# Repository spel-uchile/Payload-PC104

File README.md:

# Payload-PC104 #

This repository contains schematics and footprints of the PC104 standard for CubeSats' payloads. 
These designs are compatible with Eagle and KiCad PCB design software.
The footprints have also a suggested PCB boundary that facilitates the cable management of the CubeSat.

# KiCAD #

The KiCAD's schematic includes all the necessary pins assignments to speedup the payload design. The footprint already has the edge cuts done and it follows the PC104 specification.

# Last update 10/21/2021# 
Output voltage pin update on StackBreakout with Molex picoBlade

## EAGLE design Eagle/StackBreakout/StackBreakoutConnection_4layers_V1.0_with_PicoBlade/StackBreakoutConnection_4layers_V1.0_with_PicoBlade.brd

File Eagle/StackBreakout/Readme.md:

Readme - Stack Breakout

Stack Breakout - 4 capas

Historial

2021-11-24
Correción de error en conexión I2C v2. Los pines actuales son SCL (H1.9), SDA (H1.11). 
La versión anterior tiene las conexiones invertidas, es decir, el pin SCL estaba en H1.11, y SDA en H1.9.

2021-10-21
Se actualizan el orden los OUT pin de voltaje de acuerdo a la configuración de pinout de SPEL.

2020-08-12
Se incorpora conector con conexión I2C y UART.

2020-07-27 - V1.0
Se genera la placa de acuerdo a los diseños (dxf) enviados por Elías Obreque.
Se genera la placa usando cuatro capas
Se configurar parámetros genéricos (y más comunes) para el chequeo de errores (DRC - Design Rule Check)

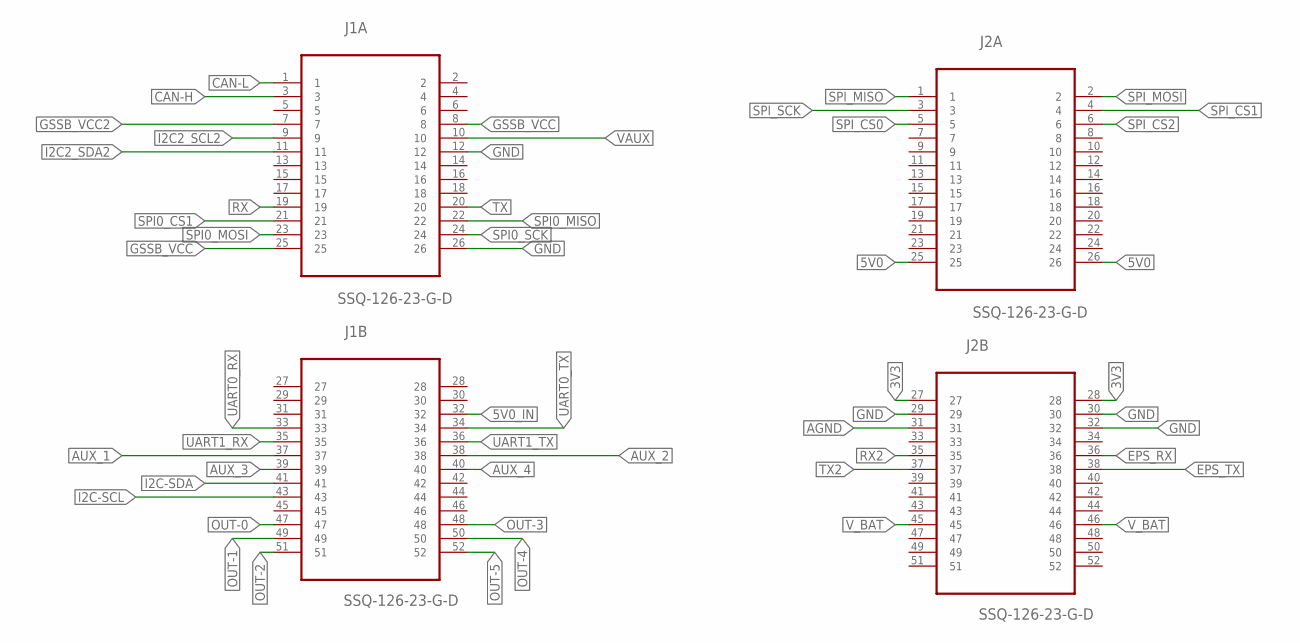
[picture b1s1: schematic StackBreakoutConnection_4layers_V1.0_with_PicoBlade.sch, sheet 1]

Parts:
J1, J2: SSQ-126-23-G-D; SAMTEC_SSQ-126-23-G-D

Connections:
3V3: J2.27, J2.28; also elsewhere on the board
5V0: J2.25, J2.26; also elsewhere on the board
5V0_IN: J1.32; also elsewhere on the board
AGND: J2.31; also elsewhere on the board
AUX_1: J1.37; also elsewhere on the board
AUX_2: J1.38; also elsewhere on the board
AUX_3: J1.39; also elsewhere on the board
AUX_4: J1.40; also elsewhere on the board
CAN-H: J1.3; also elsewhere on the board
CAN-L: J1.1; also elsewhere on the board
EPS_RX: J2.36; also elsewhere on the board
EPS_TX: J2.38; also elsewhere on the board
GND: J1.12, J1.26, J2.29, J2.30, J2.32; also elsewhere on the board
GSSB_VCC: J1.8, J1.25; also elsewhere on the board
GSSB_VCC2: J1.7; also elsewhere on the board
I2C2_SCL2: J1.9; also elsewhere on the board
I2C2_SDA2: J1.11; also elsewhere on the board
I2C-SCL: J1.43; also elsewhere on the board
I2C-SDA: J1.41; also elsewhere on the board
OUT-0: J1.47; also elsewhere on the board
OUT-1: J1.49; also elsewhere on the board
OUT-2: J1.51; also elsewhere on the board
OUT-3: J1.48; also elsewhere on the board
OUT-4: J1.50; also elsewhere on the board
OUT-5: J1.52; also elsewhere on the board
RX: J1.19
RX2: J2.35
SPI0_CS1: J1.21; also elsewhere on the board
SPI0_MISO: J1.22; also elsewhere on the board
SPI0_MOSI: J1.23; also elsewhere on the board
SPI0_SCK: J1.24; also elsewhere on the board
SPI_CS0: J2.5
SPI_CS1: J2.4
SPI_CS2: J2.6
SPI_MISO: J2.1
SPI_MOSI: J2.2
SPI_SCK: J2.3
TX: J1.20
TX2: J2.37
UART0_RX: J1.33; also elsewhere on the board
UART0_TX: J1.34; also elsewhere on the board
UART1_RX: J1.35; also elsewhere on the board
UART1_TX: J1.36; also elsewhere on the board
VAUX: J1.10; also elsewhere on the board
V_BAT: J2.45, J2.46; also elsewhere on the board

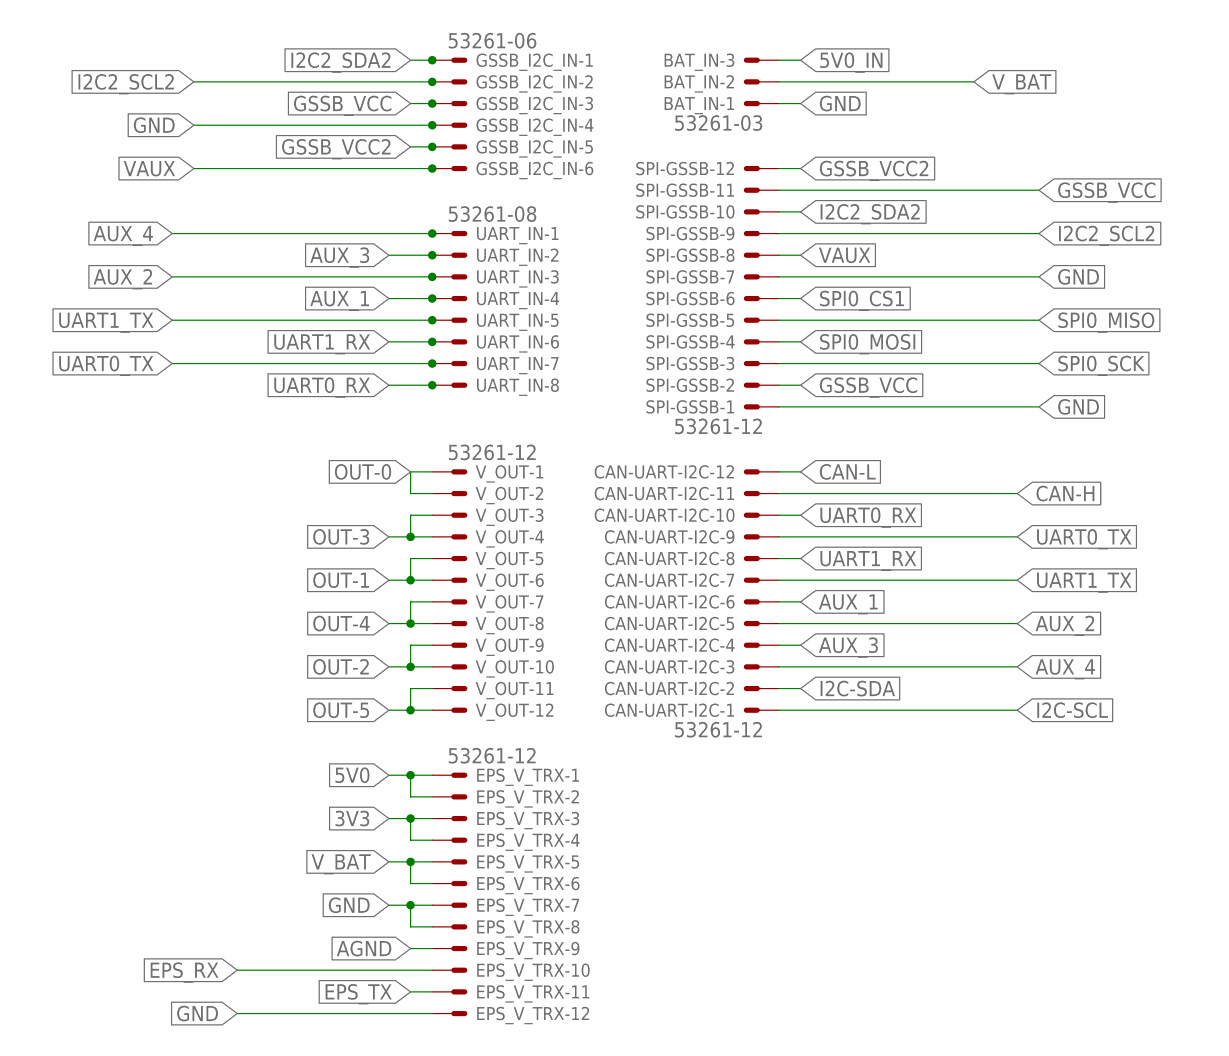
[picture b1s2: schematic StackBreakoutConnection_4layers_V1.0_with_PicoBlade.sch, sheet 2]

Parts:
BAT_IN: 53261-03
CAN-UART-I2C: 53261-12
EPS_V_TRX: 53261-12
GSSB_I2C_IN: 53261-06
SPI-GSSB: 53261-12
UART_IN: 53261-08
V_OUT: 53261-12

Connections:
3V3: EPS_V_TRX.3, EPS_V_TRX.4; also elsewhere on the board
5V0: EPS_V_TRX.1, EPS_V_TRX.2; also elsewhere on the board
5V0_IN: BAT_IN.3; also elsewhere on the board
AGND: EPS_V_TRX.9; also elsewhere on the board
AUX_1: CAN-UART-I2C.6, UART_IN.4; also elsewhere on the board
AUX_2: CAN-UART-I2C.5, UART_IN.3; also elsewhere on the board
AUX_3: CAN-UART-I2C.4, UART_IN.2; also elsewhere on the board
AUX_4: CAN-UART-I2C.3, UART_IN.1; also elsewhere on the board
CAN-H: CAN-UART-I2C.11; also elsewhere on the board
CAN-L: CAN-UART-I2C.12; also elsewhere on the board
EPS_RX: EPS_V_TRX.10; also elsewhere on the board
EPS_TX: EPS_V_TRX.11; also elsewhere on the board
GND: BAT_IN.1, EPS_V_TRX.7, EPS_V_TRX.8, EPS_V_TRX.12, GSSB_I2C_IN.4, SPI-GSSB.1, SPI-GSSB.7; also elsewhere on the board
GSSB_VCC: GSSB_I2C_IN.3, SPI-GSSB.2, SPI-GSSB.11; also elsewhere on the board
GSSB_VCC2: GSSB_I2C_IN.5, SPI-GSSB.12; also elsewhere on the board
I2C2_SCL2: GSSB_I2C_IN.2, SPI-GSSB.9; also elsewhere on the board
I2C2_SDA2: GSSB_I2C_IN.1, SPI-GSSB.10; also elsewhere on the board
I2C-SCL: CAN-UART-I2C.1; also elsewhere on the board
I2C-SDA: CAN-UART-I2C.2; also elsewhere on the board
OUT-0: V_OUT.1, V_OUT.2; also elsewhere on the board
OUT-1: V_OUT.5, V_OUT.6; also elsewhere on the board
OUT-2: V_OUT.9, V_OUT.10; also elsewhere on the board
OUT-3: V_OUT.3, V_OUT.4; also elsewhere on the board
OUT-4: V_OUT.7, V_OUT.8; also elsewhere on the board
OUT-5: V_OUT.11, V_OUT.12; also elsewhere on the board
SPI0_CS1: SPI-GSSB.6; also elsewhere on the board
SPI0_MISO: SPI-GSSB.5; also elsewhere on the board
SPI0_MOSI: SPI-GSSB.4; also elsewhere on the board
SPI0_SCK: SPI-GSSB.3; also elsewhere on the board
UART0_RX: CAN-UART-I2C.10, UART_IN.8; also elsewhere on the board
UART0_TX: CAN-UART-I2C.9, UART_IN.7; also elsewhere on the board
UART1_RX: CAN-UART-I2C.8, UART_IN.6; also elsewhere on the board
UART1_TX: CAN-UART-I2C.7, UART_IN.5; also elsewhere on the board
VAUX: GSSB_I2C_IN.6, SPI-GSSB.8; also elsewhere on the board
V_BAT: BAT_IN.2, EPS_V_TRX.5, EPS_V_TRX.6; also elsewhere on the board

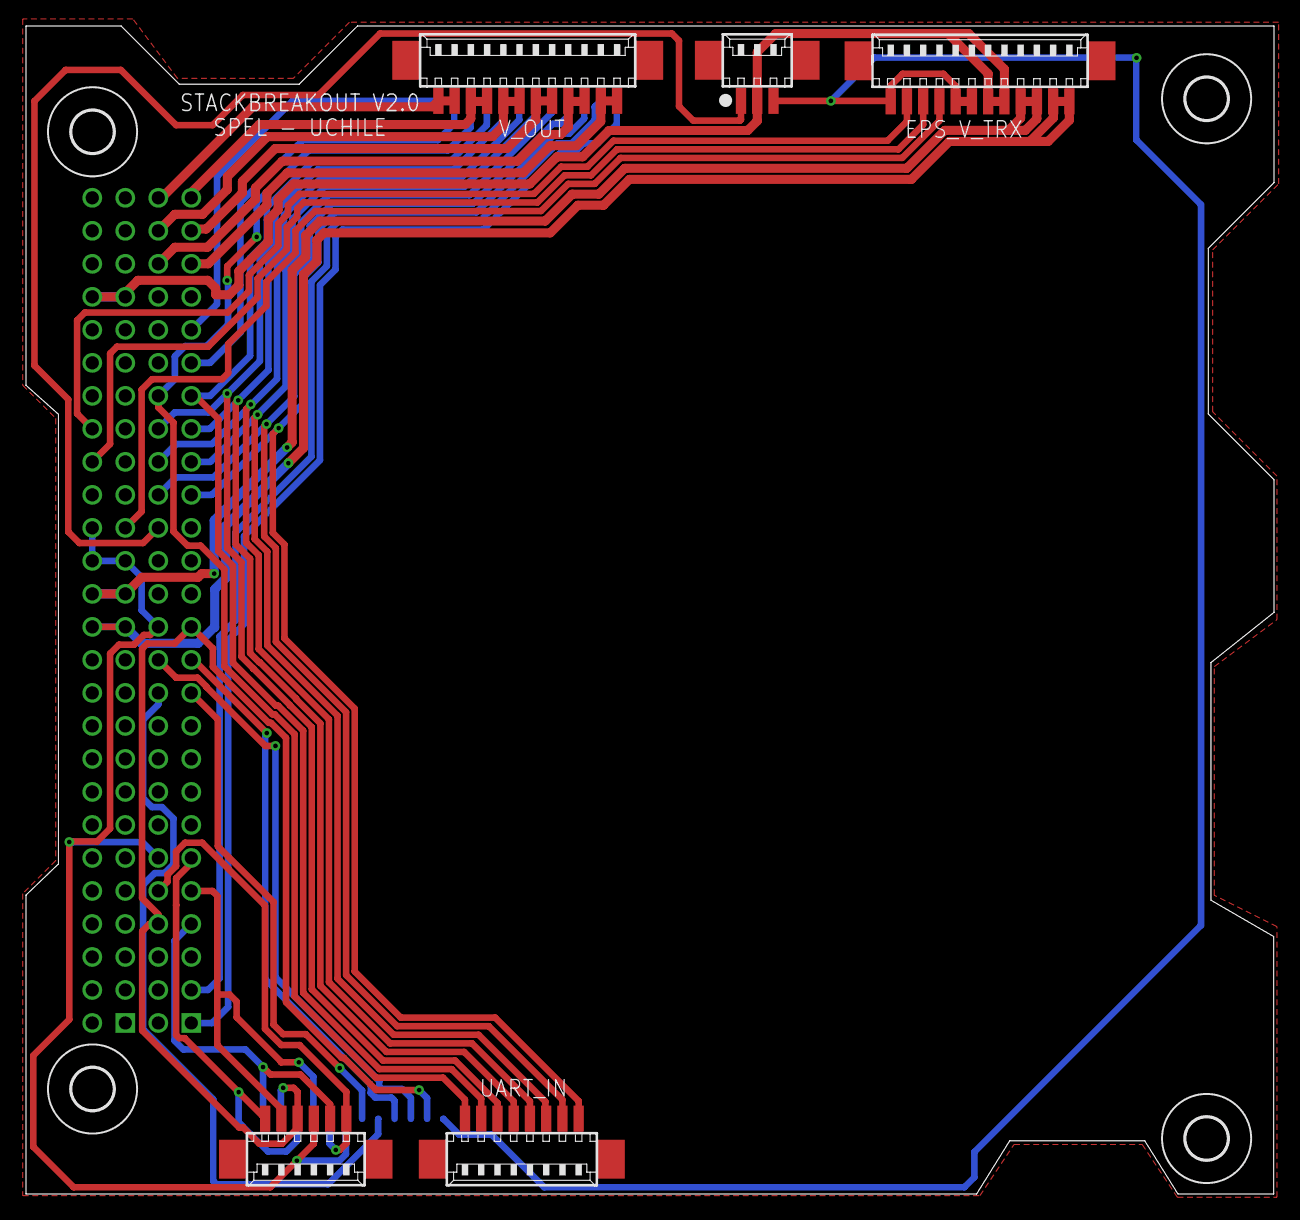
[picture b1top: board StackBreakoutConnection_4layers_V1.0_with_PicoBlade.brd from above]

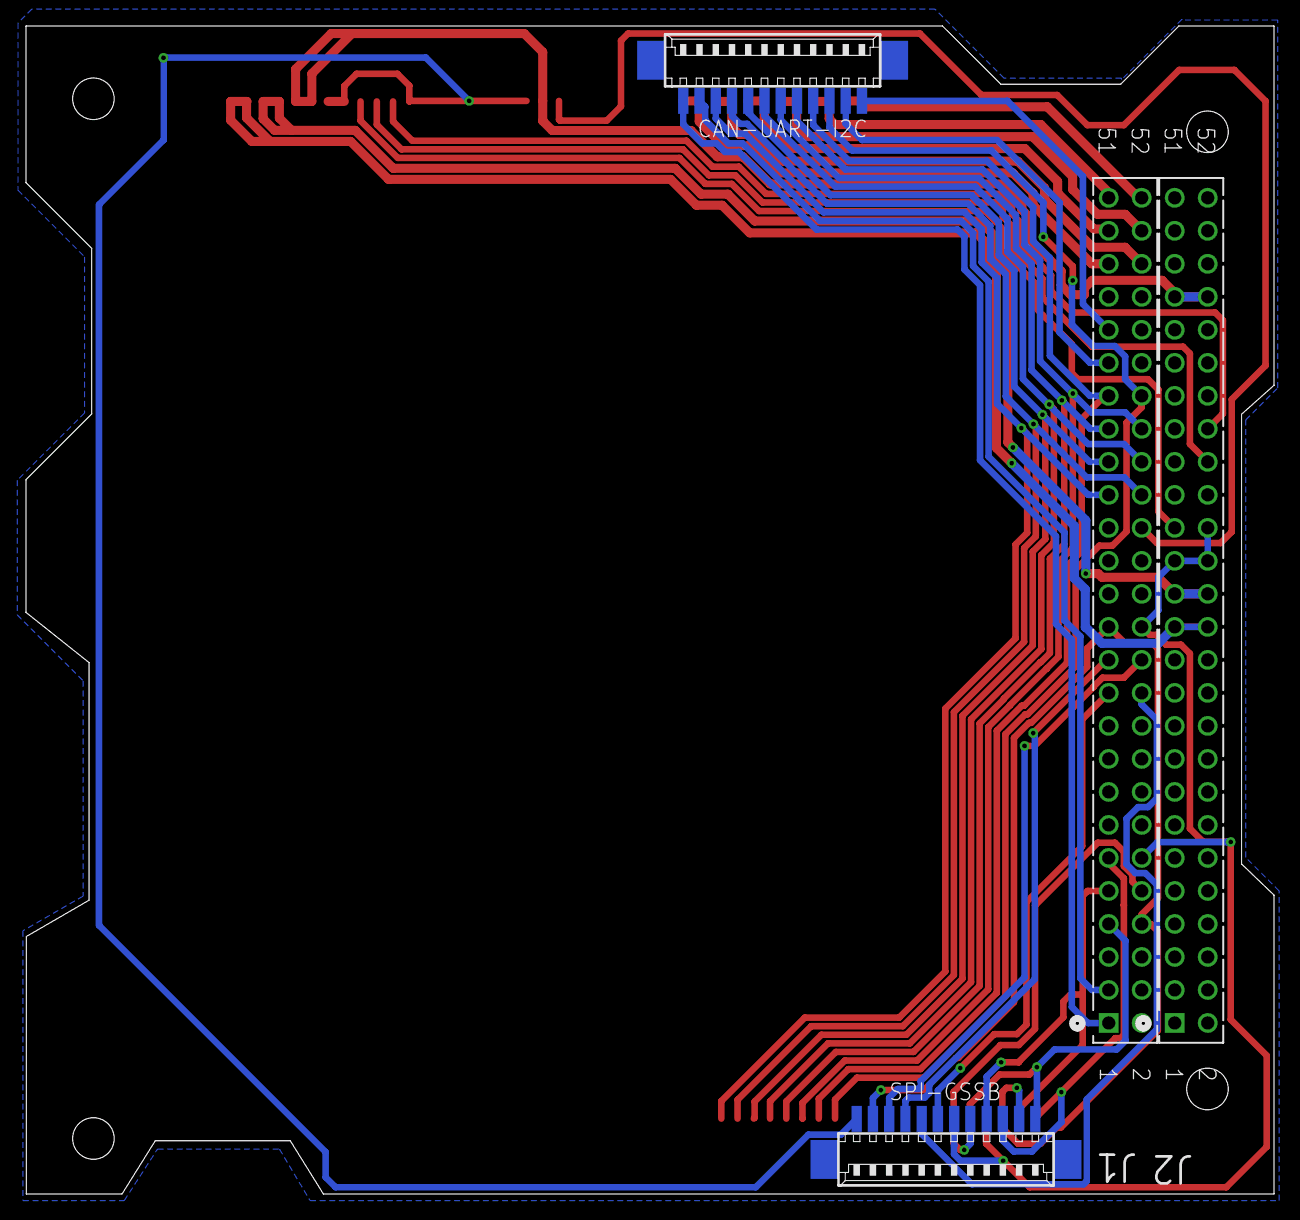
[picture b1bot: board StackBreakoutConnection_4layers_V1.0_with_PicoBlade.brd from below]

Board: 4 copper layers, 96.0 x 89.9 mm, 13 parts (4 on the bottom side), 35 nets.

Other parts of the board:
GND: 3,2
U$1, U$2, U$4: 3,2

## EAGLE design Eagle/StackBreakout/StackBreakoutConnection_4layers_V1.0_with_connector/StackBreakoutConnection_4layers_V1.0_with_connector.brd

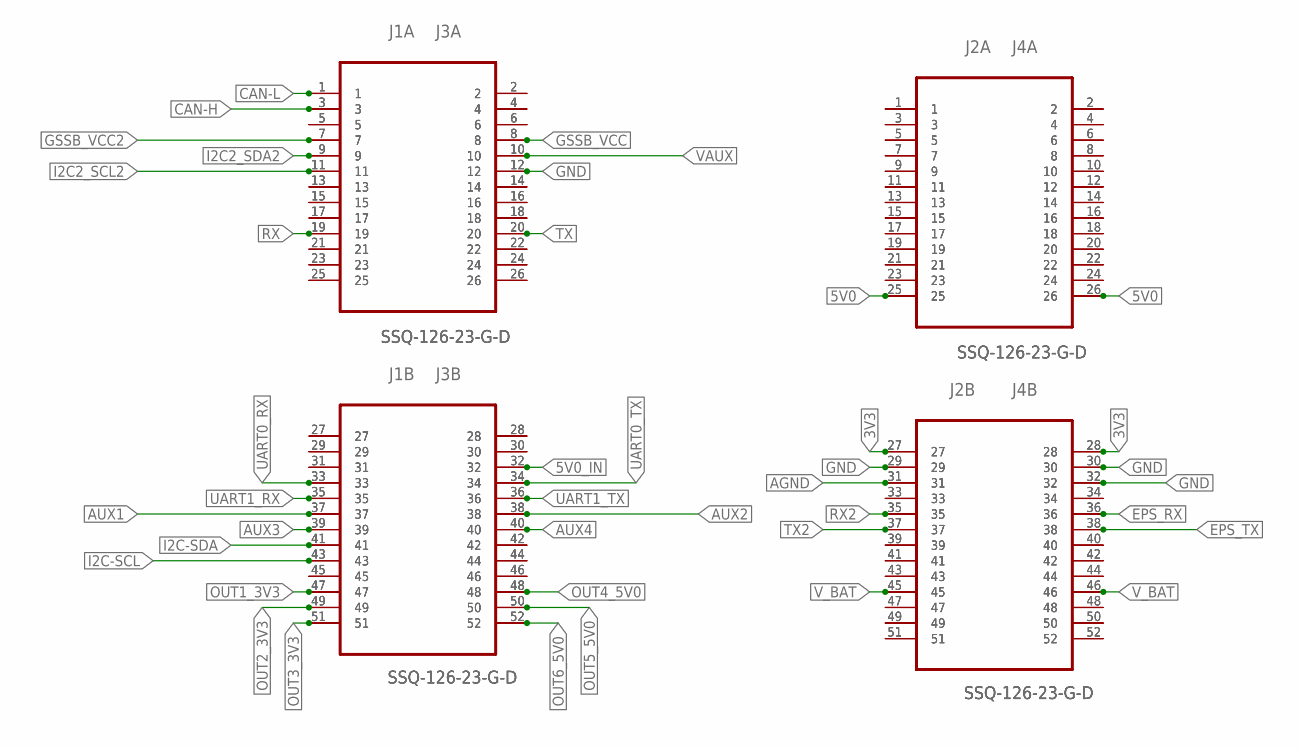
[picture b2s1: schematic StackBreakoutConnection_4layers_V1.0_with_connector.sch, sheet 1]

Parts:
J1, J2, J3, J4: SSQ-126-23-G-D; SAMTEC_SSQ-126-23-G-D

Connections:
3V3: J2.27, J2.28, J4.27, J4.28
5V0: J2.25, J2.26, J4.25, J4.26
5V0_IN: J1.32, J3.32
AGND: J2.31, J4.31
CAN-H: J1.3, J3.3
CAN-L: J1.1, J3.1
EPS_RX: J2.36, J4.36
EPS_TX: J2.38, J4.38
GND: J1.12, J2.29, J2.30, J2.32, J3.12, J4.29, J4.30, J4.32; also elsewhere on the board
GSSB_VCC: J1.8, J3.8; also elsewhere on the board
GSSB_VCC2: J1.7, J3.7; also elsewhere on the board
I2C2_SCL2: J1.11, J3.11; also elsewhere on the board
I2C2_SDA2: J1.9, J3.9; also elsewhere on the board
I2C-SCL: J1.43, J3.43
I2C-SDA: J1.41, J3.41
unnamed: J1.5, J3.5
unnamed: J1.13, J3.13
unnamed: J1.15, J3.15
unnamed: J1.17, J3.17
unnamed: J1.21, J3.21
unnamed: J1.23, J3.23
unnamed: J1.25, J3.25
unnamed: J1.2, J3.2
unnamed: J1.4, J3.4
unnamed: J1.6, J3.6
unnamed: J1.14, J3.14
unnamed: J1.16, J3.16
unnamed: J1.18, J3.18
unnamed: J1.22, J3.22
unnamed: J1.24, J3.24
unnamed: J1.26, J3.26
unnamed: J1.27, J3.27
unnamed: J1.29, J3.29
unnamed: J1.31, J3.31
unnamed: J1.45, J3.45
unnamed: J1.28, J3.28
unnamed: J1.30, J3.30
unnamed: J1.42, J3.42
unnamed: J1.44, J3.44
unnamed: J1.46, J3.46
unnamed: J2.1, J4.1
unnamed: J2.3, J4.3
unnamed: J2.5, J4.5
unnamed: J2.7, J4.7
unnamed: J2.9, J4.9
unnamed: J2.11, J4.11
unnamed: J2.13, J4.13
unnamed: J2.15, J4.15
unnamed: J2.17, J4.17
unnamed: J2.19, J4.19
unnamed: J2.21, J4.21
unnamed: J2.23, J4.23
unnamed: J2.2, J4.2
unnamed: J2.4, J4.4
unnamed: J2.6, J4.6
unnamed: J2.8, J4.8
unnamed: J2.10, J4.10
unnamed: J2.12, J4.12
unnamed: J2.14, J4.14
unnamed: J2.16, J4.16
unnamed: J2.18, J4.18
unnamed: J2.20, J4.20
unnamed: J2.22, J4.22
unnamed: J2.24, J4.24
unnamed: J2.33, J4.33
unnamed: J2.39, J4.39
unnamed: J2.41, J4.41
unnamed: J2.43, J4.43
unnamed: J2.47, J4.47
unnamed: J2.49, J4.49
unnamed: J2.51, J4.51
unnamed: J2.34, J4.34
unnamed: J2.40, J4.40
unnamed: J2.42, J4.42
unnamed: J2.44, J4.44
unnamed: J2.48, J4.48
unnamed: J2.50, J4.50
unnamed: J2.52, J4.52
OUT1_3V3: J1.47, J3.47
OUT2_3V3: J1.49, J3.49
OUT3_3V3: J1.51, J3.51
OUT4_5V0: J1.48, J3.48
OUT5_5V0: J1.50, J3.50
OUT6_5V0: J1.52, J3.52
RX: J1.19, J3.19
RX2: J2.35, J4.35
TX: J1.20, J3.20
TX2: J2.37, J4.37
UART0_RX: J1.33, J3.33; also elsewhere on the board
UART0_TX: J1.34, J3.34; also elsewhere on the board
UART1_RX: J1.35, J3.35; also elsewhere on the board
UART1_TX: J1.36, J3.36; also elsewhere on the board
VAUX: J1.10, J3.10; also elsewhere on the board
V_BAT: J2.45, J2.46, J4.45, J4.46

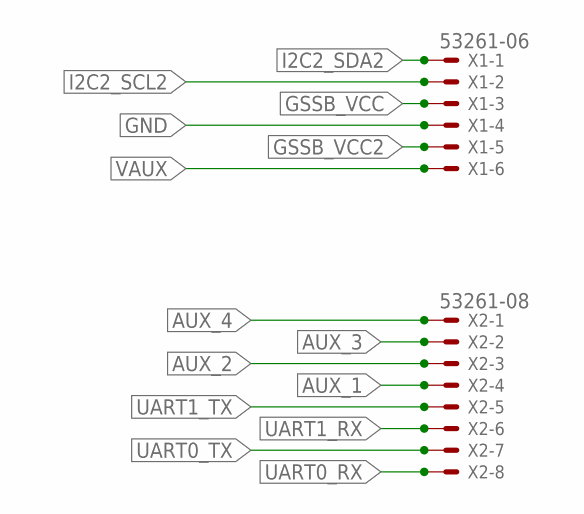
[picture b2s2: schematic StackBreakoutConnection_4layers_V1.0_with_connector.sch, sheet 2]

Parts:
X1: 53261-06
X2: 53261-08

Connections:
GND: X1.4; also elsewhere on the board
GSSB_VCC: X1.3; also elsewhere on the board
GSSB_VCC2: X1.5; also elsewhere on the board
I2C2_SCL2: X1.2; also elsewhere on the board
I2C2_SDA2: X1.1; also elsewhere on the board
UART0_RX: X2.8; also elsewhere on the board
UART0_TX: X2.7; also elsewhere on the board
UART1_RX: X2.6; also elsewhere on the board
UART1_TX: X2.5; also elsewhere on the board
VAUX: X1.6; also elsewhere on the board

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
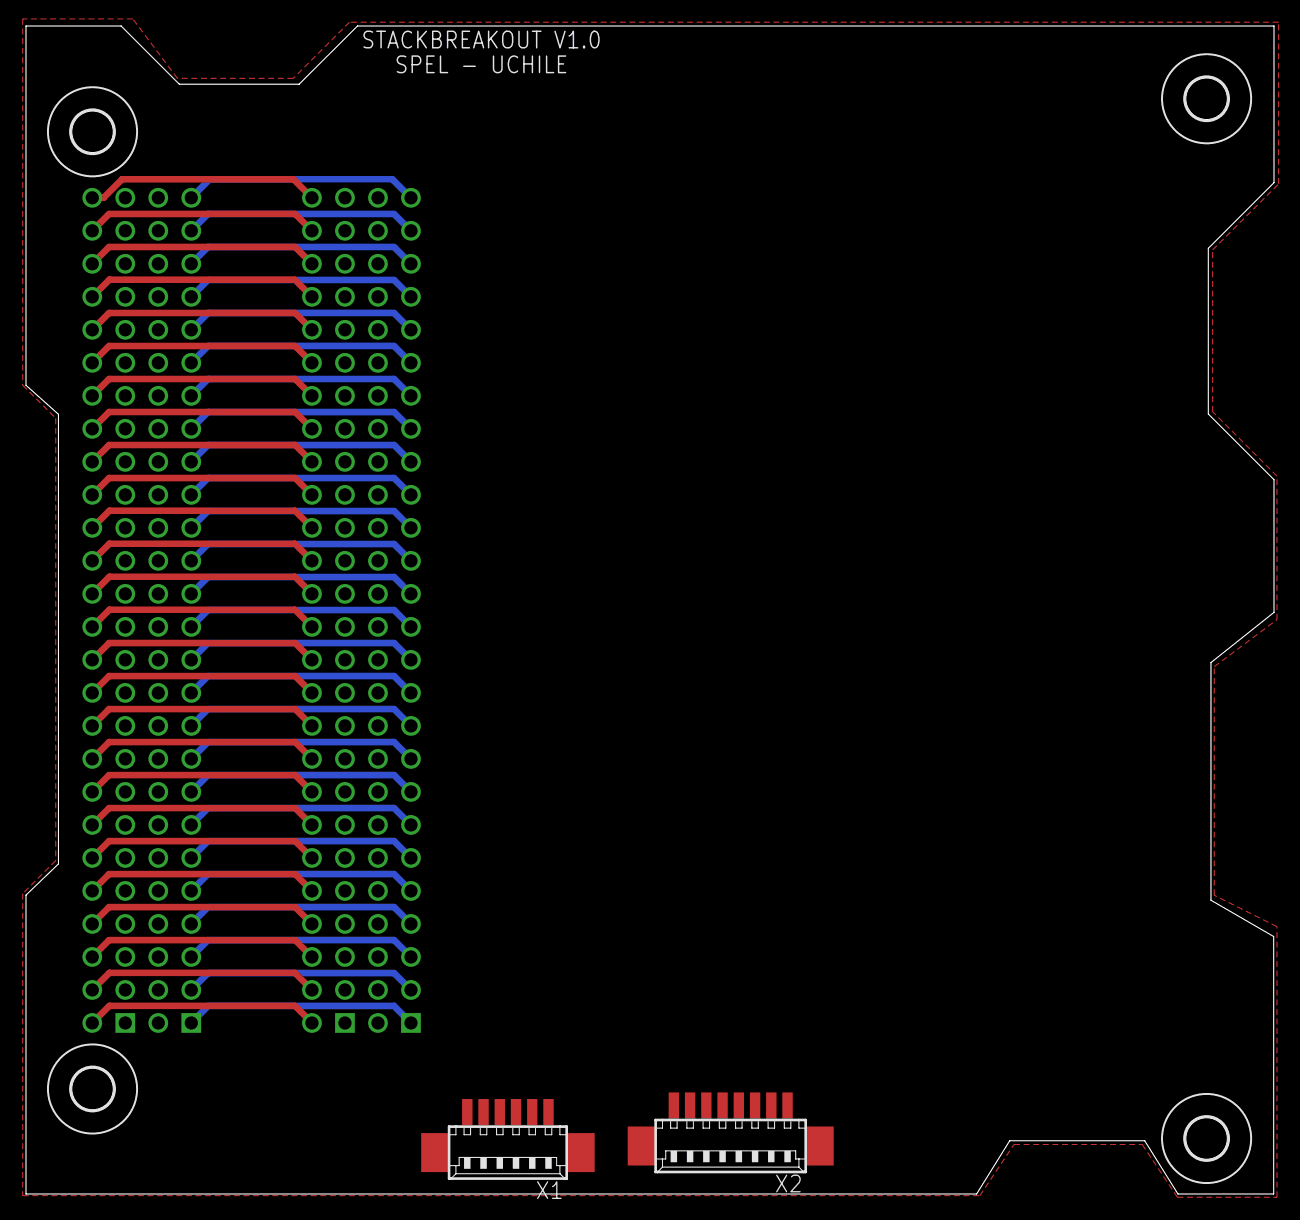
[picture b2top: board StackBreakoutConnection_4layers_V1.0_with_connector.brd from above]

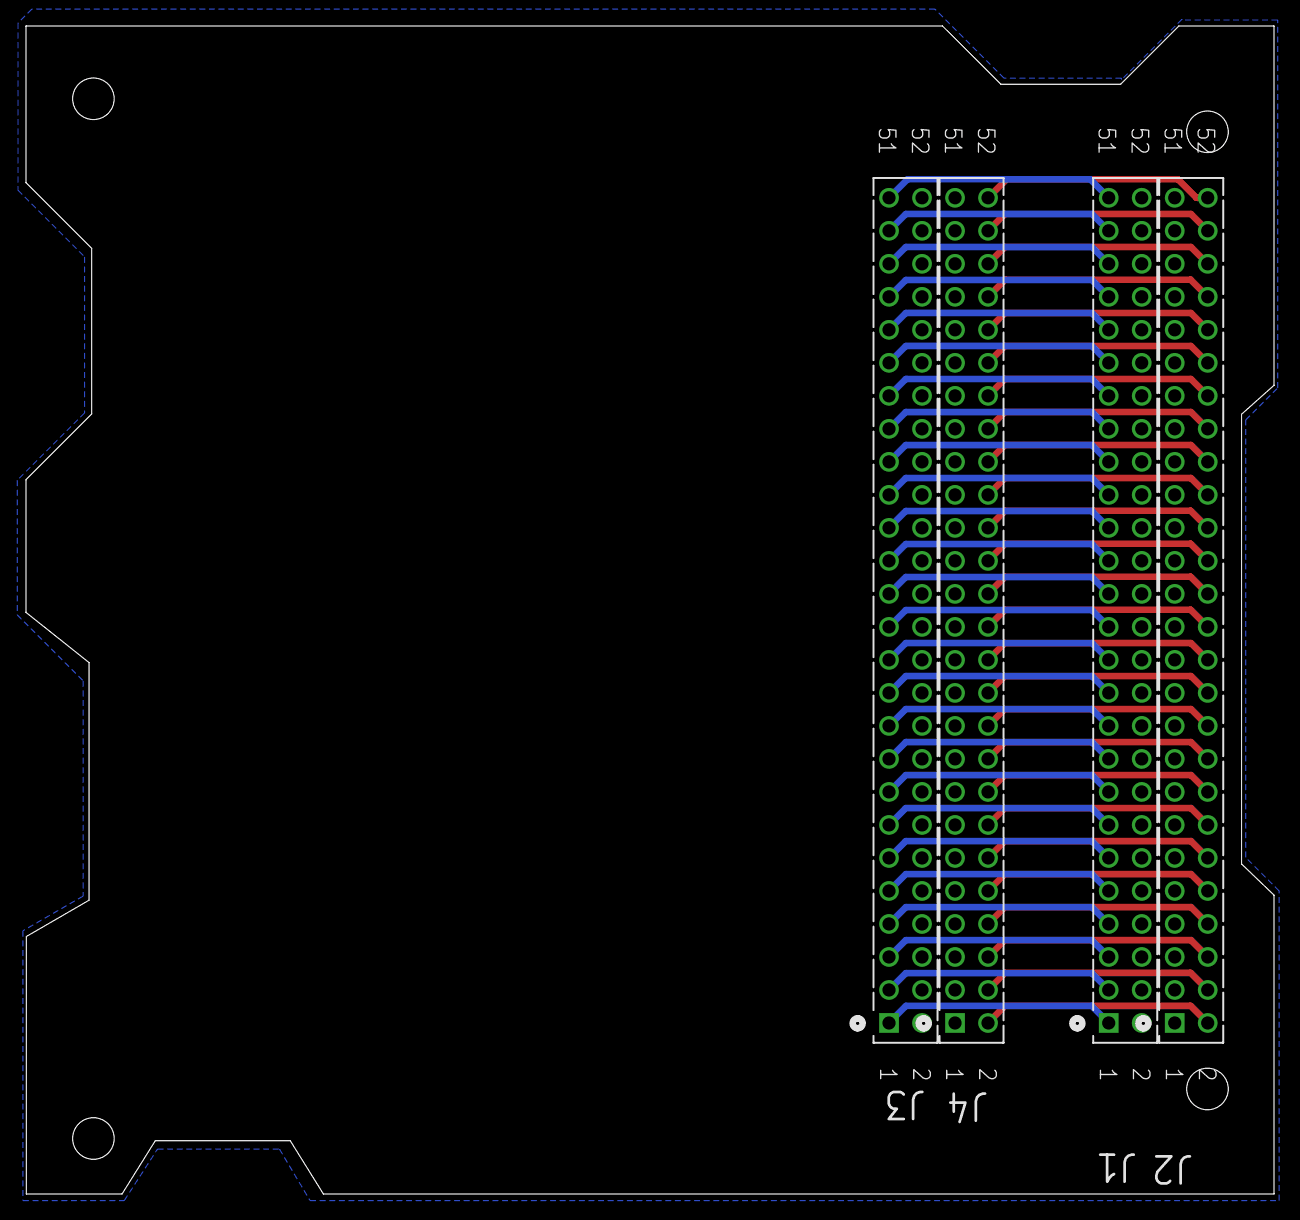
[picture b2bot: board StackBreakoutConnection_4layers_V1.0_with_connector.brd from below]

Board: 4 copper layers, 96.0 x 89.9 mm, 10 parts (4 on the bottom side), 98 nets.

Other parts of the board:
U$1, U$2, U$3, U$4: 3,2

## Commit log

2018-11-14 Added a KiCad library for the payload template, following the CubeSat and PC104 standards. It includes an schematic with the SUCHAI 2 and 3 pinout and a footprint.
2018-11-14 Added a brief project description.
2018-11-14 Added silk mask with the boundaries of the stack and the mechanical holes. Also changed the first pin's shape from circular to rectangular.
2018-11-15 Eagle library_ PCB
2018-11-16 Changed footprint's outer lines from F.SilkS layer to Edge.Cuts. Also increased drill size of the mechanical holes.
2018-11-20 Increased the pad's size of the mechanical drills.
2018-11-20 Fixed error in pin spacing (changed from 2.56 mm to 2.54 mm).
2018-11-28 Changed NPTH to Through-holes, so that they can be connected to ground.
2019-06-11 Increased drill and pad size.
2019-06-14 Increased pad size.
2019-06-26 Pad with different diameter
2019-06-26 delete
2019-07-05 Updated the symbol and footprint of the PC104 standard.
2020-02-25 Update to Eagle version of PC104 stack schematic and dimensions
2020-02-25 Removing unversioned files
2020-02-25 Pad-Pinout with 1.75 mm d
2020-03-20 refactoring
2020-03-20 removing temporary file
2020-04-08 Conexiones entre Stack
2020-04-25 Updated the README file with some picture and a little description.
2020-07-27 First version of 4 layers Stack Breakout PCB
2020-08-12 StackBreakoutWithConnector
2020-08-12 Historial_update
2020-08-25 Corrección de Aux_x
2021-07-29 PC104 picoblade
2021-10-21 Output voltage pin update
2021-10-21 Readme
2021-10-21 Readme update
2021-11-24 update i2c pinout
2022-11-02 Added more space for cable management and smoothened the edges.
2022-11-02 Updated the footprint for the latest KiCAD version.
2022-11-02 Updated the image to the new version.
2022-11-02 Replaced the symbol library to the new supported version.
